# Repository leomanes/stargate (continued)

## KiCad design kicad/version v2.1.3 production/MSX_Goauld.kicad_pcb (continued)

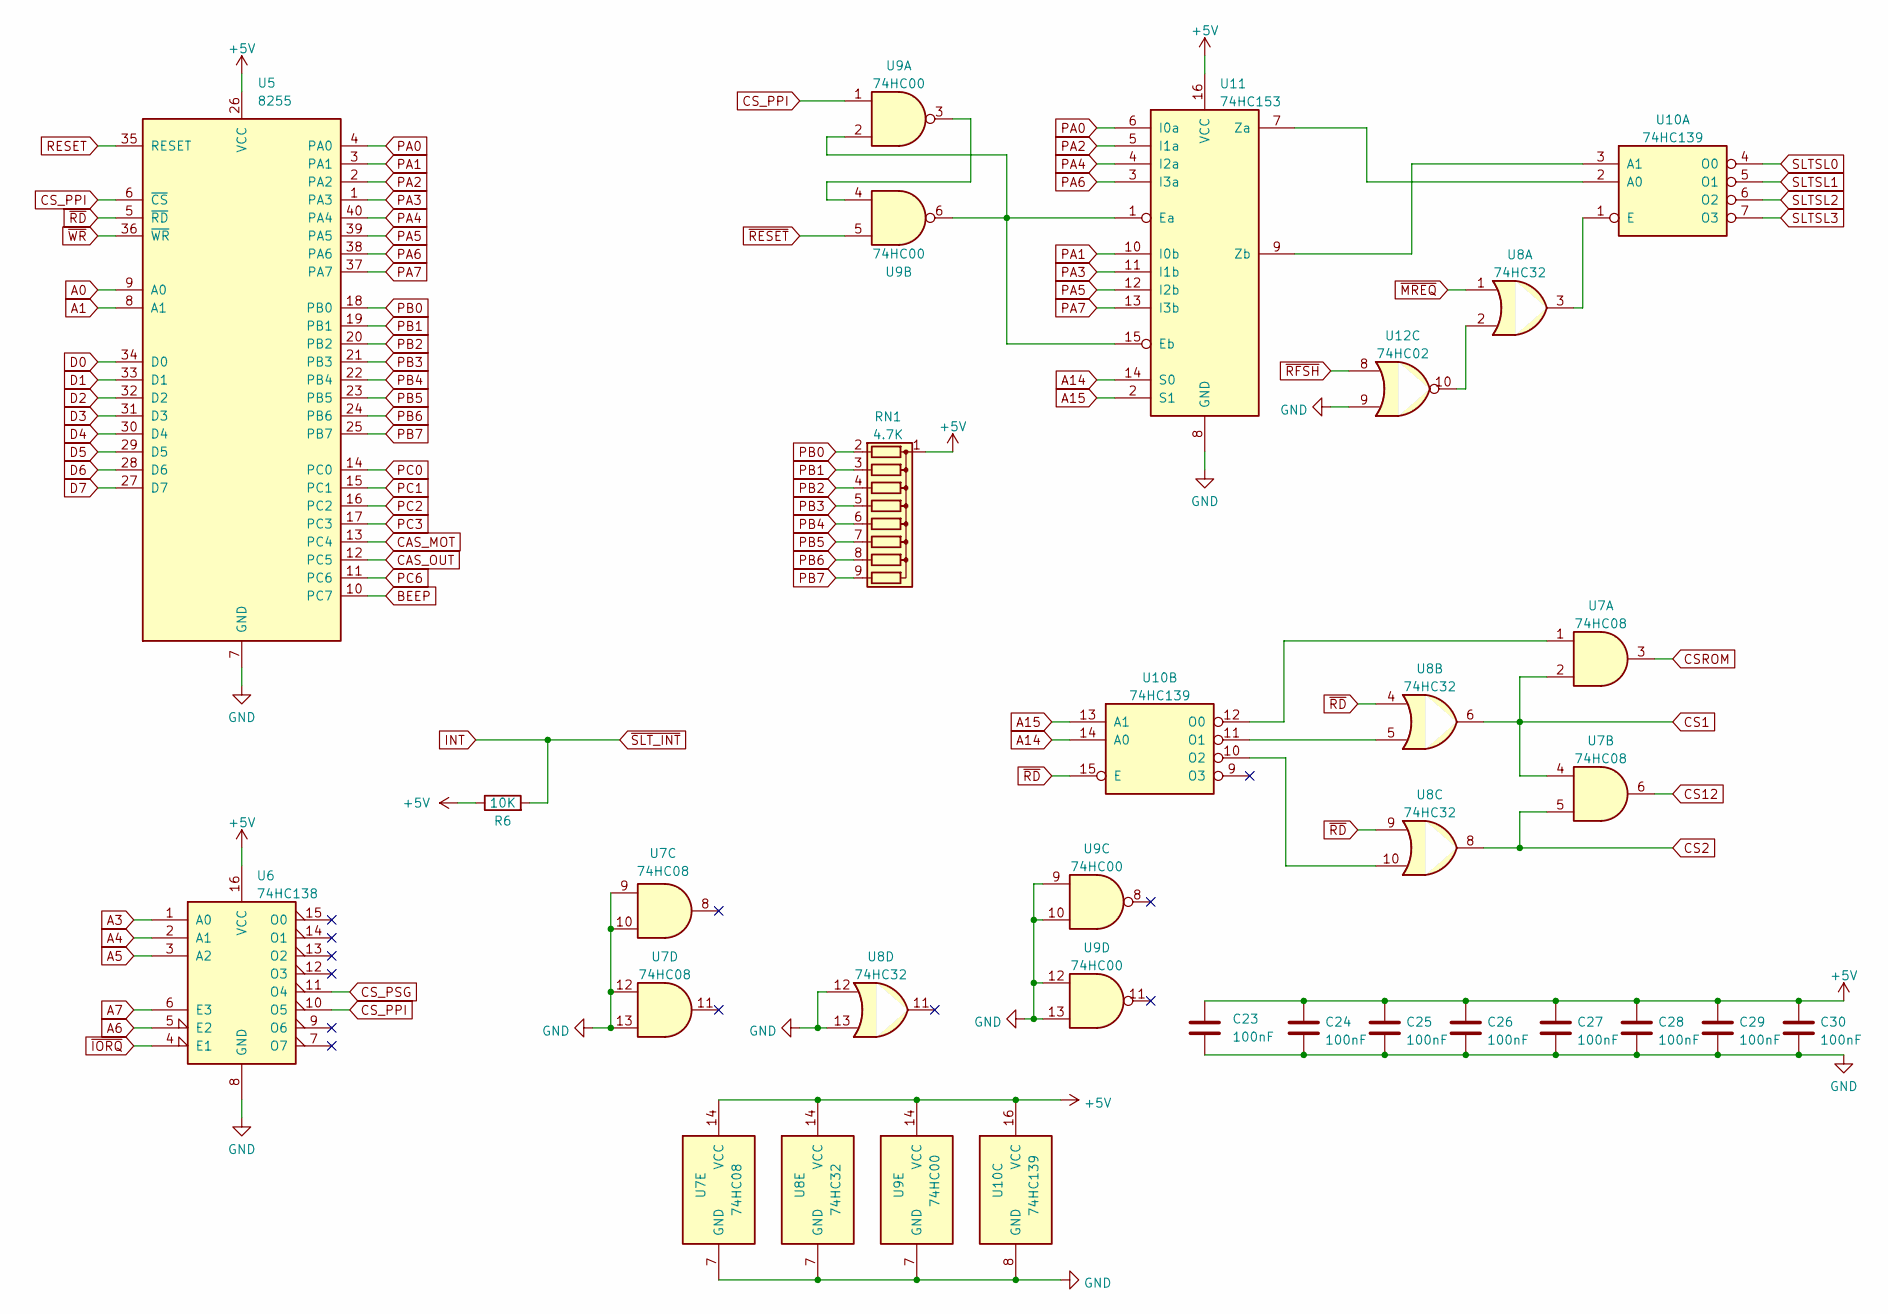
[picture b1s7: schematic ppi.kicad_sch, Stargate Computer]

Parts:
C23, C24, C25, C26, C27, C28, C29, C30: 100nF; CP_P5.00mm
R6: 10K; R_Axial_DIN0204_L3.6mm_D1.6mm_P7.62mm_Horizontal
RN1: 4.7K; R_Array_SIP9
U5: 8255; DIP-40_W15.24mm_LongPads
U6: 74HC138; DIP-16_W7.62mm_LongPads
U7: 74HC08; DIP-14_W7.62mm_LongPads
U8: 74HC32; DIP-14_W7.62mm_LongPads
U9: 74HC00; DIP-14_W7.62mm_LongPads
U10: 74HC139; DIP-16_W7.62mm_LongPads
U11: 74HC153; DIP-16_W7.62mm_LongPads
U12: 74HC02; DIP-14_W7.62mm_LongPads

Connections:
+5V: C23.1, C24.1, C25.1, C26.1, C27.1, C28.1, C29.1, C30.1, R6.1, RN1.1 (common), U5.26 (VCC), U6.16 (VCC), U7.14 (VCC), U8.14 (VCC), U9.14 (VCC), U10.16 (VCC), U11.16 (VCC); also elsewhere on the board
A0: U5.9 (A0); also elsewhere on the board
A1: U5.8 (A1); also elsewhere on the board
A3: U6.1 (A0); also elsewhere on the board
A4: U6.2 (A1); also elsewhere on the board
A5: U6.3 (A2); also elsewhere on the board
A6: U6.5 (E2); also elsewhere on the board
A7: U6.6 (E3); also elsewhere on the board
A14: U10.14 (A0), U11.14 (S0); also elsewhere on the board
A15: U10.13 (A1), U11.2 (S1); also elsewhere on the board
BEEP: U5.10 (PC7); also elsewhere on the board
CAS_MOT: U5.13 (PC4); also elsewhere on the board
CAS_OUT: U5.12 (PC5); also elsewhere on the board
CS1: U7.2, U7.4, U8.6; also elsewhere on the board
CS2: U7.5, U8.8; also elsewhere on the board
CS12: U7.6; also elsewhere on the board
CSROM: U7.3
CS_PPI: U5.6 (~CS), U6.10 (O5), U9.1
CS_PSG: U6.11 (O4); also elsewhere on the board
D0: U5.34 (D0); also elsewhere on the board
D1: U5.33 (D1); also elsewhere on the board
D2: U5.32 (D2); also elsewhere on the board
D3: U5.31 (D3); also elsewhere on the board
D4: U5.30 (D4); also elsewhere on the board
D5: U5.29 (D5); also elsewhere on the board
D6: U5.28 (D6); also elsewhere on the board
D7: U5.27 (D7); also elsewhere on the board
GND: C23.2, C24.2, C25.2, C26.2, C27.2, C28.2, C29.2, C30.2, U5.7 (GND), U6.8 (GND), U7.7 (GND), U7.9, U7.10, U7.12, U7.13, U8.7 (GND), U8.12, U8.13, U9.7 (GND), U9.9, U9.10, U9.12, U9.13, U10.8 (GND), U11.8 (GND), U12.9; also elsewhere on the board
INT: R6.2; also elsewhere on the board
unnamed: U9.3, U9.4
unnamed: U10.2 (A0), U11.7 (Za)
unnamed: U10.3 (A1), U11.9 (Zb)
unnamed: U8.3, U10.1 (E)
unnamed: U7.1, U10.12 (O0)
unnamed: U8.5, U10.11 (O1)
unnamed: U8.10, U10.10 (O2)
unnamed: U9.2, U9.6, U11.1 (Ea), U11.15 (Eb)
unnamed: U8.2, U12.10
PA0: U5.4 (PA0), U11.6 (I0a)
PA1: U5.3 (PA1), U11.10 (I0b)
PA2: U5.2 (PA2), U11.5 (I1a)
PA3: U5.1 (PA3), U11.11 (I1b)
PA4: U5.40 (PA4), U11.4 (I2a)
PA5: U5.39 (PA5), U11.12 (I2b)
PA6: U5.38 (PA6), U11.3 (I3a)
PA7: U5.37 (PA7), U11.13 (I3b)
PB0: RN1.2 (R1), U5.18 (PB0); also elsewhere on the board
PB1: RN1.3 (R2), U5.19 (PB1); also elsewhere on the board
PB2: RN1.4 (R3), U5.20 (PB2); also elsewhere on the board
PB3: RN1.5 (R4), U5.21 (PB3); also elsewhere on the board
PB4: RN1.6 (R5), U5.22 (PB4); also elsewhere on the board
PB5: RN1.7 (R6), U5.23 (PB5); also elsewhere on the board
PB6: RN1.8 (R7), U5.24 (PB6); also elsewhere on the board
PB7: RN1.9 (R8), U5.25 (PB7); also elsewhere on the board
PC0: U5.14 (PC0); also elsewhere on the board
PC1: U5.15 (PC1); also elsewhere on the board
PC2: U5.16 (PC2); also elsewhere on the board
PC3: U5.17 (PC3); also elsewhere on the board
PC6: U5.11 (PC6); also elsewhere on the board
RESET: U5.35 (RESET); also elsewhere on the board
SLTSL0: U10.4 (O0)
SLTSL1: U10.5 (O1); also elsewhere on the board
SLTSL2: U10.6 (O2); also elsewhere on the board
SLTSL3: U10.7 (O3)
~IORQ: U6.4 (E1); also elsewhere on the board
~MREQ: U8.1; also elsewhere on the board
~RD: U5.5 (~RD), U8.4, U8.9, U10.15 (E); also elsewhere on the board
~RESET: U9.5; also elsewhere on the board
~RFSH: U12.8; also elsewhere on the board
~WR: U5.36 (~WR); also elsewhere on the board

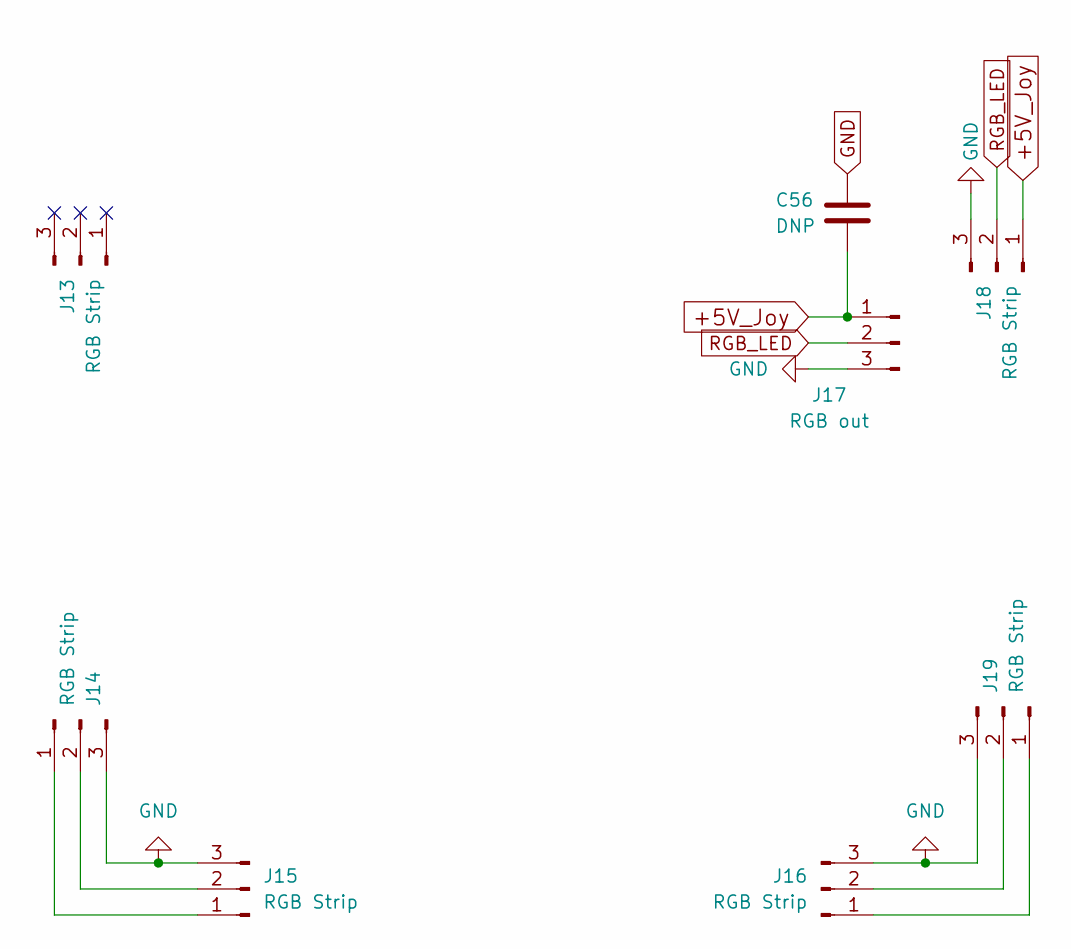
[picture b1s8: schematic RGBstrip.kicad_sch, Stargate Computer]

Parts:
C56: DNP; CP_P5.00mm
J13, J15, J19: RGB Strip; ledstrip_end
J14, J16, J18: RGB Strip; ledstrip
J17: RGB out; FanPinHeader_1x03_P2.54mm_Vertical

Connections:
+5V_Joy: C56.1, J17.1, J18.1; also elsewhere on the board
GND: C56.2, J14.3, J15.3, J16.3, J17.3, J18.3, J19.3; also elsewhere on the board
unnamed: J14.1, J15.1
unnamed: J14.2, J15.2
unnamed: J16.1, J19.1
unnamed: J16.2, J19.2
RGB_LED: J17.2, J18.2; also elsewhere on the board

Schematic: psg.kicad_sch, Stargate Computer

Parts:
C37, C38, C39, C40, C41, C60: 10uF; CP_Radial_D5.0mm_P2.50mm
C42: DNP; CP_EIA-7343-31_Kemet-D
C43, C44, C45, C46: 100nF; CP_P5.00mm
F2: Fuse; THT+SMD(Fuse)
J6: Audio Out; Conn_RCA_Right
J7: Joystick1; Conn_Dsub_DE9M
J8: Joystick2; Conn_Dsub_DE9M
JP7: 50on; SolderJumper-2_P1.3mm_Open_Pad1.0x1.5mm
Q1: BC558; TO-92
R7, R44: 10K; R_Axial_DIN0204_L3.6mm_D1.6mm_P7.62mm_Horizontal
R8, R9: 4K7; R_Axial_DIN0204_L3.6mm_D1.6mm_P7.62mm_Horizontal
R10, R11: 20K; R_Axial_DIN0204_L3.6mm_D1.6mm_P7.62mm_Horizontal
R12: 2K2; R_Axial_DIN0204_L3.6mm_D1.6mm_P7.62mm_Horizontal
R13: 470R; R_Axial_DIN0204_L3.6mm_D1.6mm_P7.62mm_Horizontal
R45: 150; R_Axial_DIN0204_L3.6mm_D1.6mm_P7.62mm_Horizontal
RN3: 10K; R_Array_SIP9
RN4: 10K; R_Array_SIP5
RV1: 50K; TrimPotLargeHole
U12: 74HC02; DIP-14_W7.62mm_LongPads
U19: YM2149; DIP-40_W15.24mm_LongPads
U20: 74LS07; DIP-14_W7.62mm_LongPads
U21, U22: 74HC157; DIP-16_W7.62mm_LongPads

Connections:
+5V: C42.1, C43.1, C44.1, C45.1, C46.1, F2.1, R44.2, RN3.1 (common), RN4.1 (common), U12.14 (VCC), U19.25 (A8), U19.28 (BC2), U19.40 (VCC), U20.14 (VCC), U21.16 (VCC), U22.16 (VCC); also elsewhere on the board
+5V_Joy: F2.2, J7.5, J8.5; also elsewhere on the board
A0: U12.5; also elsewhere on the board
Amp_In: J6.1 (In), R8.2, R9.2, R10.2, R11.2, R12.2, R45.2; also elsewhere on the board
BEEP: C41.1; also elsewhere on the board
CAS_FEEDBACK: RV1.3; also elsewhere on the board
CAS_IN: U19.14 (IOA7); also elsewhere on the board
CLK_PSG: U19.22 (CLOCK); also elsewhere on the board
CS_PSG: U12.3, U12.6; also elsewhere on the board
D0: U19.37 (DA0); also elsewhere on the board
D1: U19.36 (DA1); also elsewhere on the board
D2: U19.35 (DA2); also elsewhere on the board
D3: U19.34 (DA3); also elsewhere on the board
D4: U19.33 (DA4); also elsewhere on the board
D5: U19.32 (DA5); also elsewhere on the board
D6: U19.31 (DA6); also elsewhere on the board
D7: U19.30 (DA7); also elsewhere on the board
GND: C42.2, C43.2, C44.2, C45.2, C46.2, J6.2 (Ext), J7.9, J8.9 (PAD), JP7.2 (B), R13.2, RV1.1, U12.7 (GND), U12.11, U12.12, U19.1 (VSS), U19.24 (~A9), U20.7 (GND), U20.11, U20.13, U21.8 (GND), U21.15 (E), U22.8 (GND), U22.10 (I1c), U22.11 (I0c), U22.13 (I1d), U22.14 (I0d), U22.15 (E); also elsewhere on the board
IOA0: U19.21 (IOA0), U21.4 (Za)
IOA1: U19.20 (IOA1), U21.7 (Zb)
IOA2: U19.19 (IOA2), U21.9 (Zc)
IOA3: U19.18 (IOA3), U21.12 (Zd)
IOA4: U19.17 (IOA4), U22.4 (Za)
IOA5: U19.16 (IOA5), U22.7 (Zb)
IOB0: U19.13 (IOB0), U20.1
IOB1: U19.12 (IOB1), U20.3
IOB2: U19.11 (IOB2), U20.5
IOB3: U19.10 (IOB3), U20.9
IOB4: J7.8, U19.9 (IOB4)
IOB5: J8.8, U19.8 (IOB5)
IOB6: U19.7 (IOB6), U21.1 (S), U22.1 (S)
J1_DOWN: J7.2, RN3.4 (R3), U21.5 (I0b)
J1_LEFT: J7.3, RN3.6 (R5), U21.11 (I0c)
J1_RIGHT: J7.4, RN3.8 (R7), U21.14 (I0d)
J1_TR1: J7.6, RN4.5 (R4), U20.2, U22.2 (I0a)
J1_TR2: J7.7, RN4.3 (R2), U20.4, U22.5 (I0b)
J1_UP: J7.1, RN3.2 (R1), U21.2 (I0a)
J2_DOWN: J8.2, RN3.5 (R4), U21.6 (I1b)
J2_LEFT: J8.3, RN3.7 (R6), U21.10 (I1c)
J2_RIGHT: J8.4, RN3.9 (R8), U21.13 (I1d)
J2_TR1: J8.6, RN4.4 (R3), U20.6, U22.3 (I1a)
J2_TR2: J8.7, RN4.2 (R1), U20.8, U22.6 (I1b)
J2_UP: J8.1, RN3.3 (R2), U21.3 (I1a)
KANA_LED: U19.6 (IOB7); also elsewhere on the board
unnamed: C37.2, R12.1
unnamed: C38.2, R8.1
unnamed: C39.2, R9.1
unnamed: C40.1, RV1.2
unnamed: C40.2, R10.1
unnamed: C41.2, R11.1
unnamed: C60.2, R45.1
unnamed: JP7.1 (A), R44.1, U19.15 (IOA6)
unnamed: Q1.2 (B), R7.2
unnamed: C37.1, Q1.1 (C)
unnamed: Q1.3 (E), R13.1, U19.3 (A), U19.4 (B), U19.38 (C)
unnamed: U12.4, U19.29 (BC1)
unnamed: U12.1, U19.27 (BDIR)
PSG_Mute: R7.1; also elsewhere on the board
SOUNDIN1: C38.1; also elsewhere on the board
SOUNDIN2: C39.1; also elsewhere on the board
TANGOUT: C60.1; also elsewhere on the board
~RESET: U19.23 (~RESET); also elsewhere on the board
~WR: U12.2; also elsewhere on the board

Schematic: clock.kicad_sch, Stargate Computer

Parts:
C18: 100nF; CP_P5.00mm
FREQ1: SI5351; si5351
JP2: XTAL ON; SolderJumper-2_P1.3mm_Open_Pad1.0x1.5mm
JP3: XTAL>SYS; SolderJumper-2_P1.3mm_Open_Pad1.0x1.5mm
U2: 74HC74; DIP-14_W7.62mm_LongPads
Y1: 3.579545MHZ; Oscillator_DIP-8

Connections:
+5V: C18.1, FREQ1.7 (VIN), U2.1 (~R), U2.4 (~S), U2.14 (VCC), Y1.8 (Vcc); also elsewhere on the board
CLK_CPU: FREQ1.3 (2), JP3.1 (A); also elsewhere on the board
CLK_PSG: FREQ1.2 (1), U2.5 (Q); also elsewhere on the board
CLK_SYS: FREQ1.1 (0), JP2.2 (B), JP3.2 (B), U2.3 (C); also elsewhere on the board
ESP_SCL: FREQ1.4 (SCL); also elsewhere on the board
ESP_SDA: FREQ1.5 (SDA); also elsewhere on the board
GND: C18.2, FREQ1.6 (GND), U2.7 (GND), U2.8 (~Q), U2.9 (Q), U2.10 (~S), U2.11 (C), U2.12 (D), Y1.4 (GND); also elsewhere on the board
unnamed: JP2.1 (A), Y1.5 (OUT)
unnamed: U2.2 (D), U2.6 (~Q)

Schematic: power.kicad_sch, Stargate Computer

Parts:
C1, C2, C3: DNP; CP_Radial_D5.0mm_P2.50mm
C4: 470uF; CP_Radial_D10.0mm_P5.00mm
C5, C6: 220uF; CP_Radial_D8.0mm_P3.50mm
C7, C8, C9, C10, C11, C12, C15, C16: 100nF; CP_P5.00mm
C13, C14: DNP; CP_EIA-7343-31_Kemet-D
C17: 220uF; CP_Radial_D5.0mm_P2.50mm
D1: PWR_LED; LED_D5.0mm
D2: 1N5817; D_DO-41_SOD81_P7.62mm_Horizontal
F1: Fuse; THT+SMD(Fuse)
J1: Barrel_Jack; BarrelJack_Horizontal
J2: USB Module; USB-C Decoy
J3: DD1718PA 12V; dd1718pa_down
J22: Conn_5V; PinHeader_1x02_P2.54mm_Vertical
JP1: ESP PWR; PinHeader_1x02_P2.54mm_Vertical
OVP1: 5V; OVP
R1: 470R; R_Axial_DIN0204_L3.6mm_D1.6mm_P7.62mm_Horizontal
SW1: ON/OFF; SW_RF1-1A-DC-2-R-1
TP1: GND; TestPoint_THTPad_D2.5mm_Drill1.2mm
TP2: +3V3 TN; TestPoint_THTPad_D2.5mm_Drill1.2mm
TP3: +3V3 WiFi; TestPoint_THTPad_D2.5mm_Drill1.2mm
TP4: -12V; TestPoint_THTPad_D2.5mm_Drill1.2mm
TP5: +12V; TestPoint_THTPad_D2.5mm_Drill1.2mm
TP6: +5V; TestPoint_THTPad_D2.5mm_Drill1.2mm
U1: AMS1117-3.3; SOT-223-3_TabPin2

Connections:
+3V3: C17.1, JP1.2 (B), TP3.1; also elsewhere on the board
+5V: C1.1, C4.1, C7.1, C10.1, C15.1, D2.2 (A), J3.1, J22.2, OVP1.2 (OUT), R1.1, TP6.1, U1.3 (VI); also elsewhere on the board
+12V: C3.1, C6.1, C9.1, C12.1, J3.3, TP5.1; also elsewhere on the board
-12V: C2.2, C5.2, C8.1, C11.1, J3.5, TP4.1; also elsewhere on the board
GND: C1.2, C2.1, C3.2, C4.2, C5.1, C6.2, C7.2, C8.2, C9.2, C10.2, C11.2, C12.2, C13.2, C14.2, C15.2, C16.2, C17.2, D1.1 (K), J1.2, J1.3, J2.2, J3.2, J3.4, J22.1, OVP1.3 (GND), OVP1.4 (GND), TP1.1, U1.1 (GND); also elsewhere on the board
unnamed: D1.2 (A), R1.2
unnamed: F1.1, SW1.2
unnamed: J1.1, J2.1, SW1.1
unnamed: C16.1, JP1.1 (A), U1.2 (VO)
unnamed: F1.2, OVP1.1 (IN)
VCC_3V3: TP2.1; also elsewhere on the board
VCC_4V7: C13.1, C14.1, D2.1 (K); also elsewhere on the board

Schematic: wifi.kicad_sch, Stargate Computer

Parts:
D4: WIFI_LED; LED_D3.0mm
J10: I2C; PinHeader_1x04_P2.54mm_Vertical
J11: UART; PinHeader_1x04_P2.54mm_Vertical
R27, R28, R29, R30, R31, R32, R39: 10K; R_Axial_DIN0204_L3.6mm_D1.6mm_P7.62mm_Horizontal
R33: 3K3; R_Axial_DIN0204_L3.6mm_D1.6mm_P7.62mm_Horizontal
R34, R35, R36: 470; R_Axial_DIN0204_L3.6mm_D1.6mm_P7.62mm_Horizontal
R37: 220R; R_Axial_DIN0204_L3.6mm_D1.6mm_P7.62mm_Horizontal
R38: 1M; R_Axial_DIN0204_L3.6mm_D1.6mm_P7.62mm_Horizontal
SW3: SW1; SW_Tactile_SPST_Angled_PTS645Vx83-2LFS
SW4: SW2; SW_Tactile_SPST_Angled_PTS645Vx83-2LFS
SW5: Reset ESP; SW_PUSH_6mm
SW6: UP; SW_PUSH_6mm
SW7: DOWN; SW_PUSH_6mm
SW8: SELECT; SW_PUSH_6mm
SW9: Program ESP; SW_PUSH_6mm
U24: ESP-12F

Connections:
+3V3: J10.2, J11.2, R27.2, R28.2, R30.1, R31.1, R33.1, R39.1, U24.8 (VCC); also elsewhere on the board
ESP_SCL: J10.3, U24.20 (GPIO5); also elsewhere on the board
ESP_SDA: J10.4, U24.19 (GPIO4); also elsewhere on the board
GND: D4.1 (K), J10.1, J11.1, R29.1, R32.1, R36.2, R38.1, SW3.2, SW4.2, SW5.2, SW9.2, U24.15 (GND); also elsewhere on the board
GPIO16: R32.2, U24.4 (GPIO16); also elsewhere on the board
unnamed: D4.2 (A), R37.2
unnamed: R33.2, R34.1, SW6.1
unnamed: R34.2, R35.1, SW7.1
unnamed: R35.2, R36.1, SW8.1
unnamed: R38.2, SW6.2, SW7.2, SW8.2, U24.2 (ADC)
unnamed: R31.2, U24.3 (EN)
unnamed: R39.2, SW9.1, U24.18 (GPIO0)
unnamed: R37.1, U24.17 (GPIO2)
unnamed: R27.1, SW3.1, U24.6 (GPIO12)
unnamed: R28.1, SW4.1, U24.7 (GPIO13)
unnamed: R30.2, SW5.1, U24.1 (RST)
PSG_Mute: R29.2, U24.16 (GPIO15); also elsewhere on the board
RGB_LED: U24.5 (GPIO14); also elsewhere on the board
WIFI_RX: J11.4, U24.21 (RXD); also elsewhere on the board
WIFI_TX: J11.3, U24.22 (TXD); also elsewhere on the board

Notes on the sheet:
OLED SCREEN CON.

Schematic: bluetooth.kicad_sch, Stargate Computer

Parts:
C55: 10uF; CP_Radial_D5.0mm_P2.50mm
J12: BT MX18; MH-M18
JP6: LR_Sel; SolderJumper-3_P1.3mm_Bridged12_Pad1.0x1.5mm_NumberLabels
Q3: BC548; TO-92
R40: 1K; R_Axial_DIN0204_L3.6mm_D1.6mm_P7.62mm_Horizontal
R41: 470; R_Axial_DIN0204_L3.6mm_D1.6mm_P7.62mm_Horizontal
U25: PC817; DIP-4_W7.62mm

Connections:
+5V: C55.1, Q3.1 (C), U25.4; also elsewhere on the board
BT_Audio: JP6.2 (C); also elsewhere on the board
GND: J12.3, U25.2; also elsewhere on the board
GPIO16: R41.1; also elsewhere on the board
unnamed: J12.1, JP6.3 (B)
unnamed: J12.2, JP6.1 (A)
unnamed: J12.4, Q3.3 (E)
unnamed: C55.2, Q3.2 (B), R40.2
unnamed: R40.1, U25.3
unnamed: R41.2, U25.1

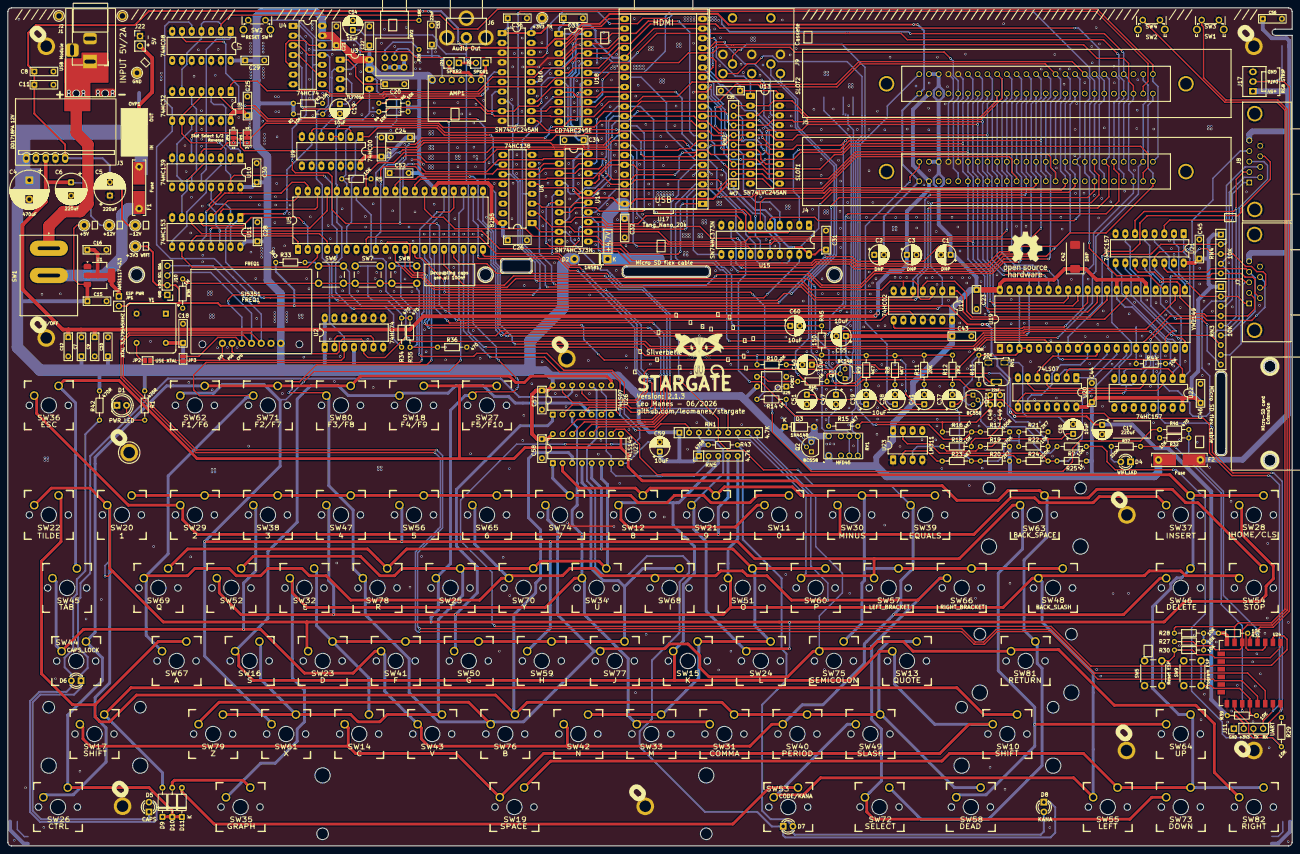
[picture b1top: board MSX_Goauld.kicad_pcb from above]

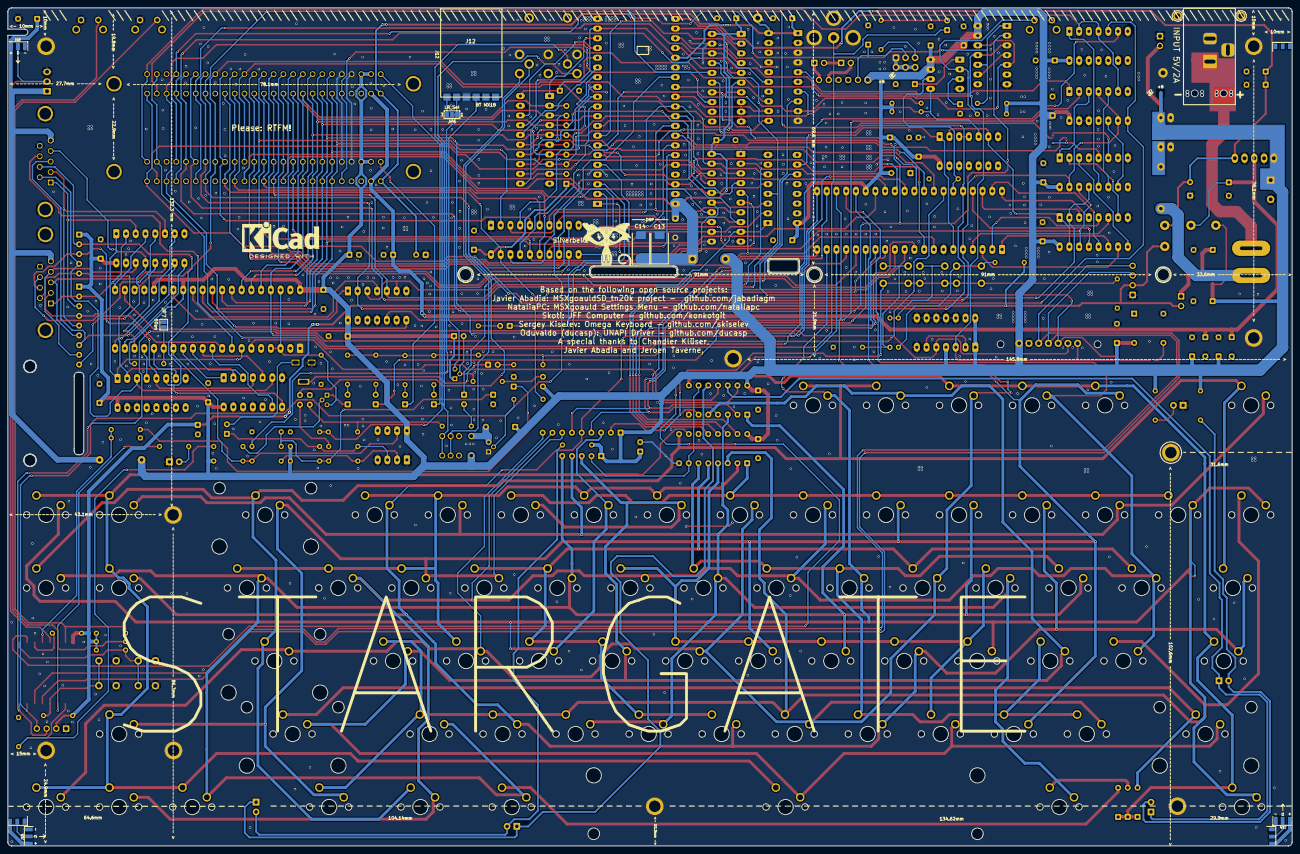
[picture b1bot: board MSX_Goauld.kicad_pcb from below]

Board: 2 copper layers, 335.0 x 218.6 mm, 293 parts (11 on the bottom side), 239 nets.

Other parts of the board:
MH01, MH02, MH03, MH04: MountingHole_3mm

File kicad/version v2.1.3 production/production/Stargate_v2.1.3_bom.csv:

Designator,Footprint,Quantity,Value,LCSC Part #
AMP1,Amp5128,1,5128,
"C1, C2, C3",CP_Radial_D5.0mm_P2.50mm,3,DNP,
"C10, C11, C12, C15, C16, C18, C20, C21, C22, C23, C24, C25, C26, C27, C28, C29, C30, C31, C32, C33, C34, C35, C36, C43, C44, C45, C46, C52, C57, C58, C7, C8, C9",CP_P5.00mm,33,100nF,
"C13, C14, C42",CP_EIA-7343-31_Kemet-D,3,DNP,
C17,CP_Radial_D5.0mm_P2.50mm,1,220uF,
"C19, C37, C38, C39, C40, C41, C47, C50, C51, C54, C55, C59, C60",CP_Radial_D5.0mm_P2.50mm,13,10uF,
C4,CP_Radial_D10.0mm_P5.00mm,1,470uF,
"C48, C49",C_Disc_D3.0mm_W2.0mm_P2.50mm,2,22nF,
"C5, C6",CP_Radial_D8.0mm_P3.50mm,2,220uF,
C53,CP_P5.00mm,1,22nF,
C56,CP_P5.00mm,1,DNP,
D1,LED_D5.0mm,1,PWR_LED,
"D10, D11, D3, D9",D_DO-35_SOD27_P7.62mm_Horizontal,4,1N4148,
D2,D_DO-41_SOD81_P7.62mm_Horizontal,1,1N5817,
D4,LED_D3.0mm,1,WIFI_LED,
"D5, D6",LED_D3.0mm,2,CAPS,
"D7, D8",LED_D3.0mm,2,KANA,
"F1, F2",THT+SMD(Fuse),2,Fuse,
FREQ1,si5351,1,SI5351,
"HOLE1, HOLE12, HOLE2, HOLE3, HOLE4, HOLE5, HOLE6, HOLE7, HOLE8, HOLE9",MountingHole_3mm_Pad_TopBottom_new,10,HOLE,
"HOLE10, HOLE11",MountingHole_2mm_Pad_TopBottom_new,2,HOLE,
J1,BarrelJack_Horizontal,1,Barrel_Jack,
J10,PinHeader_1x04_P2.54mm_Vertical,1,I2C,
J11,PinHeader_1x04_P2.54mm_Vertical,1,UART,
J12,MH-M18,1,BT MX18,
"J13, J15, J19",ledstrip_end,3,RGB Strip,
"J14, J16, J18",ledstrip,3,RGB Strip,
J17,FanPinHeader_1x03_P2.54mm_Vertical,1,RGB out,
J2,USB-C Decoy,1,USB Module,
J20,PinHeader_1x02_P2.54mm_Vertical,1,SPKR1,
J21,PinHeader_1x02_P2.54mm_Vertical,1,SPKR2,
J22,PinHeader_1x02_P2.54mm_Vertical,1,Conn_5V,
J3,dd1718pa_down,1,DD1718PA 12V,
J4,Conn_Edge_50P,1,SLOT1,
J5,Conn_Edge_50P,1,SLOT2,
J6,Conn_RCA_Right,1,Audio Out,
J7,Conn_Dsub_DE9M,1,Joystick1,
J8,Conn_Dsub_DE9M,1,Joystick2,
J9,DIN8,1,DIN-8,
JP1,PinHeader_1x02_P2.54mm_Vertical,1,ESP PWR,
JP2,SolderJumper-2_P1.3mm_Open_Pad1.0x1.5mm,1,XTAL ON,
JP3,SolderJumper-2_P1.3mm_Open_Pad1.0x1.5mm,1,XTAL>SYS,
JP7,SolderJumper-2_P1.3mm_Open_Pad1.0x1.5mm,1,50on,
OVP1,OVP,1,5V,
"Q1, Q2",TO-92,2,BC558,
Q3,TO-92,1,BC548,
"R1, R13, R42, R43",R_Axial_DIN0204_L3.6mm_D1.6mm_P7.62mm_Horizontal,4,470R,
"R10, R11",R_Axial_DIN0204_L3.6mm_D1.6mm_P7.62mm_Horizontal,2,20K,
R12,R_Axial_DIN0204_L3.6mm_D1.6mm_P7.62mm_Horizontal,1,2K2,
"R14, R25, R40",R_Axial_DIN0204_L3.6mm_D1.6mm_P7.62mm_Horizontal,3,1K,
"R15, R16, R23, R8, R9",R_Axial_DIN0204_L3.6mm_D1.6mm_P7.62mm_Horizontal,5,4K7,
R17,R_Axial_DIN0204_L3.6mm_D1.6mm_P7.62mm_Horizontal,1,100R,
"R18, R2, R22, R27, R28, R29, R3, R30, R31, R32, R39, R4, R44, R5, R6, R7",R_Axial_DIN0204_L3.6mm_D1.6mm_P7.62mm_Horizontal,16,10K,
R19,R_Axial_DIN0204_L3.6mm_D1.6mm_P7.62mm_Horizontal,1,470K,
"R20, R21",R_Axial_DIN0204_L3.6mm_D1.6mm_P7.62mm_Horizontal,2,2K7,
R24,R_Axial_DIN0204_L3.6mm_D1.6mm_P7.62mm_Horizontal,1,220K,
R26,R_Axial_DIN0204_L3.6mm_D1.6mm_P7.62mm_Horizontal,1,18K,
R33,R_Axial_DIN0204_L3.6mm_D1.6mm_P7.62mm_Horizontal,1,3K3,
"R34, R35, R36, R41",R_Axial_DIN0204_L3.6mm_D1.6mm_P7.62mm_Horizontal,4,470,
R37,R_Axial_DIN0204_L3.6mm_D1.6mm_P7.62mm_Horizontal,1,220R,
R38,R_Axial_DIN0204_L3.6mm_D1.6mm_P7.62mm_Horizontal,1,1M,
R45,R_Axial_DIN0204_L3.6mm_D1.6mm_P7.62mm_Horizontal,1,150,
RN1,R_Array_SIP9,1,4.7K,
RN2,R_Array_SIP9,1,4K7,
RN3,R_Array_SIP9,1,10K,
RN4,R_Array_SIP5,1,10K,
RN5,R_Array_SIP5,1,4.7k,
RV1,TrimPotLargeHole,1,50K,
RV2,Potentiometer_Alps_RK097_Dual_Horizontal,1,Dual Pot,
RY1,HFD45,1,HFD45,
SW1,SW_RF1-1A-DC-2-R-1,1,ON/OFF,
SW10,CHERRY_PCB_275H,1,SHIFT,
SW11,CHERRY_PCB_100H,1,0,
SW12,CHERRY_PCB_100H,1,8,
SW13,CHERRY_PCB_100H,1,QUOTE,
SW14,CHERRY_PCB_100H,1,C,
SW15,CHERRY_PCB_100H,1,K,
SW16,CHERRY_PCB_100H,1,S,
SW17,CHERRY_PCB_225H,1,SHIFT,
SW18,CHERRY_PCB_100H,1,F4/F9,
SW19,CHERRY_PCB_625H,1,SPACE,
SW2,SW_Tactile_SPST_Angled_PTS645Vx83-2LFS,1,RESET SW,
SW20,CHERRY_PCB_100H,1,1,
SW21,CHERRY_PCB_100H,1,9,
SW22,CHERRY_PCB_100H,1,TILDE,
SW23,CHERRY_PCB_100H,1,D,
SW24,CHERRY_PCB_100H,1,L,
SW25,CHERRY_PCB_100H,1,T,
SW26,CHERRY_PCB_125H,1,CTRL,
SW27,CHERRY_PCB_100H,1,F5/F10,
SW28,CHERRY_PCB_100H,1,HOME/CLS,
SW29,CHERRY_PCB_100H,1,2,
SW3,SW_Tactile_SPST_Angled_PTS645Vx83-2LFS,1,SW1,
SW30,CHERRY_PCB_100H,1,MINUS,
SW31,CHERRY_PCB_100H,1,COMMA,
SW32,CHERRY_PCB_100H,1,E,
SW33,CHERRY_PCB_100H,1,M,
SW34,CHERRY_PCB_100H,1,U,
SW35,CHERRY_PCB_125H,1,GRAPH,
SW36,CHERRY_PCB_100H,1,ESC,
SW37,CHERRY_PCB_100H,1,INSERT,
SW38,CHERRY_PCB_100H,1,3,
SW39,CHERRY_PCB_100H,1,EQUALS,
SW4,SW_Tactile_SPST_Angled_PTS645Vx83-2LFS,1,SW2,
SW40,CHERRY_PCB_100H,1,PERIOD,
SW41,CHERRY_PCB_100H,1,F,
SW42,CHERRY_PCB_100H,1,N,
SW43,CHERRY_PCB_100H,1,V,
SW44,CHERRY_PCB_175H,1,CAPS_LOCK,
SW45,CHERRY_PCB_150H,1,TAB,
SW46,CHERRY_PCB_100H,1,DELETE,
SW47,CHERRY_PCB_100H,1,4,
SW48,CHERRY_PCB_150H,1,BACK_SLASH,
SW49,CHERRY_PCB_100H,1,SLASH,
SW5,SW_PUSH_6mm,1,Reset ESP,
SW50,CHERRY_PCB_100H,1,G,
SW51,CHERRY_PCB_100H,1,O,
SW52,CHERRY_PCB_100H,1,W,
SW53,CHERRY_PCB_125H,1,CODE/KANA,
SW54,CHERRY_PCB_100H,1,STOP,
SW55,CHERRY_PCB_100H,1,LEFT,
SW56,CHERRY_PCB_100H,1,5,
SW57,CHERRY_PCB_100H,1,LEFT_BRACKET,
SW58,CHERRY_PCB_125H,1,DEAD,
SW59,CHERRY_PCB_100H,1,H,
SW6,SW_PUSH_6mm,1,UP,
SW60,CHERRY_PCB_100H,1,P,
SW61,CHERRY_PCB_100H,1,X,
SW62,CHERRY_PCB_100H,1,F1/F6,
SW63,CHERRY_PCB_200H,1,BACK_SPACE,
SW64,CHERRY_PCB_100H,1,UP,
SW65,CHERRY_PCB_100H,1,6,
SW66,CHERRY_PCB_100H,1,RIGHT_BRACKET,
SW67,CHERRY_PCB_100H,1,A,
SW68,CHERRY_PCB_100H,1,I,
SW69,CHERRY_PCB_100H,1,Q,
SW7,SW_PUSH_6mm,1,DOWN,
SW70,CHERRY_PCB_100H,1,Y,
SW71,CHERRY_PCB_100H,1,F2/F7,
SW72,CHERRY_PCB_125H,1,SELECT,
SW73,CHERRY_PCB_100H,1,DOWN,
SW74,CHERRY_PCB_100H,1,7,
SW75,CHERRY_PCB_100H,1,SEMICOLON,
SW76,CHERRY_PCB_100H,1,B,
SW77,CHERRY_PCB_100H,1,J,
SW78,CHERRY_PCB_100H,1,R,
SW79,CHERRY_PCB_100H,1,Z,
SW8,SW_PUSH_6mm,1,SELECT,
SW80,CHERRY_PCB_100H,1,F3/F8,
SW81,CHERRY_PCB_225H,1,RETURN,
SW82,CHERRY_PCB_100H,1,RIGHT,
SW9,SW_PUSH_6mm,1,Program ESP,
TP1,TestPoint_THTPad_D2.5mm_Drill1.2mm,1,GND,
TP2,TestPoint_THTPad_D2.5mm_Drill1.2mm,1,+3V3 TN,
TP3,TestPoint_THTPad_D2.5mm_Drill1.2mm,1,+3V3 WiFi,
TP4,TestPoint_THTPad_D2.5mm_Drill1.2mm,1,-12V,
TP5,TestPoint_THTPad_D2.5mm_Drill1.2mm,1,+12V,
TP6,TestPoint_THTPad_D2.5mm_Drill1.2mm,1,+5V,
U1,SOT-223-3_TabPin2,1,AMS1117-3.3,
U10,DIP-16_W7.62mm_LongPads,1,74HC139,
U11,DIP-16_W7.62mm_LongPads,1,74HC153,
U12,DIP-14_W7.62mm_LongPads,1,74HC02,
"U13, U16",DIP-20_W7.62mm_LongPads,2,SN74LVC245AN,
"U14, U15",DIP-20_W7.62mm_LongPads,2,SN74HC373N,
U17,Tang_Nano_20k,1,Tang_Nano_20k,
U18,DIP-20_W7.62mm_LongPads,1,CD74HC245E,
U19,DIP-40_W15.24mm_LongPads,1,YM2149,
"U2, U4",DIP-14_W7.62mm_LongPads,2,74HC74,
U20,DIP-14_W7.62mm_LongPads,1,74LS07,
"U21, U22",DIP-16_W7.62mm_LongPads,2,74HC157,
U23,DIP-8_W7.62mm_LongPads,1,LM311,
U24,ESP-12F,1,ESP-12F,
U25,DIP-4_W7.62mm,1,PC817,
U26,DIP-14_W7.62mm,1,74LS07,
U27,DIP-16_W7.62mm,1,74LS145,
U3,DIP-8_W7.62mm_LongPads,1,TL7705A,
U5,DIP-40_W15.24mm_LongPads,1,8255,
U6,DIP-16_W7.62mm_LongPads,1,74HC138,
U7,DIP-14_W7.62mm_LongPads,1,74HC08,
U8,DIP-14_W7.62mm_LongPads,1,74HC32,
U9,DIP-14_W7.62mm_LongPads,1,74HC00,
Y1,Oscillator_DIP-8,1,3.579545MHZ,
